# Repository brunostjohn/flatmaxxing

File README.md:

<div align="center">

# flatmaxx

**Turn a KiCad PCB into a complete CNC, laser, and electroplating job set - one command, end to end.**

</div>

`flatmaxx` takes a finished KiCad board and drives your entire home-fab bench for you: it generates Gerbers and drill files, plans isolation milling and non-copper-clearing G-code with FlatCAM, sorts every hole into the bit you actually own, burns solder-mask and solder-paste stencils on an xTool laser, drills plated/non-plated holes and cuts the board outline on a Makera CNC, and even works out the electroplating bath recipe — all from a single command, behind a live terminal UI.

> [!NOTE]
> This tool is built around one specific bench: a **Makera Carvera (Air)** CNC, **xTool M1 Ultra / F1 Ultra** lasers, and a **DIY copper electroplating** setup. It's shared as-is. Nothing stops you using it, but you'll want to retune the config to your own hardware, tools, and chemistry before trusting the output to a machine.

## Contents

- [No support — use entirely at your own risk](#-no-support--use-entirely-at-your-own-risk)
- [Installation](#installation)
- [Features](#features)
- [How it works](#how-it-works)
- [Prerequisites](#prerequisites)
- [Usage](#usage)
- [Configuration](#configuration)
- [Output layout](#output-layout)
- [Terminal experience](#terminal-experience)
- [Development](#development)

## ⚠️ No support — use entirely at your own risk

> [!CAUTION]
> **This project is provided strictly AS IS, with NO SUPPORT of any kind.**
>
> - **No tech support.** Issues opened to ask for help, setup assistance, or troubleshooting **will not be answered** and may be closed without comment.
> - **No bug guarantees.** Even legitimate bug reports **may never get a response or a fix.** Don't assume one is coming.
> - **No warranty.** Nothing here is promised to work, to keep working, or to be safe for your hardware, your materials, or you. You run it at your own risk.
>
> This is a **hobby project** I share for free in my spare time. I have a full-time job and a life, and I'm not interested in spending my free time doing unpaid tech support — I don't want my hobby to become my job. If that's a problem for you, **don't use this.**
>
> Pull requests with fixes are welcome, but I make **no commitment** to review, respond to, or merge them.

## Installation

`flatmaxx` ships as a single, codesigned **macOS arm64 (Apple Silicon)** binary. Pick whichever install path you prefer.

### Homebrew

```sh
brew tap brunostjohn/flatmaxxing https://github.com/brunostjohn/flatmaxxing
brew trust flatmaxx
brew install flatmaxx
```

Upgrade later with `brew upgrade flatmaxx`.

### Install script

Downloads the latest release into `~/.local/bin`, checksum-verified, using only standard macOS tools:

```sh
curl -fsSL https://raw.githubusercontent.com/brunostjohn/flatmaxxing/main/scripts/install.sh | sh
```

If `~/.local/bin` isn't on your `PATH`, the script prints the exact line to add. Pin a version with `FLATMAXX_VERSION=1.2.3`, or change the target with `FLATMAXX_INSTALL_DIR=...`. Installed this way, `flatmaxx update` upgrades in place (see [Updating](#updating)).

### From source

`flatmaxx` builds with [Bun](https://bun.sh) — the only thing you need.

```sh
git clone https://github.com/brunostjohn/flatmaxxing flatmaxx
cd flatmaxx
bun install
bun run build:native   # compile the native macOS accessibility module
```

Run it straight from source:

```sh
bun src/index.ts <kicad-project>
```

Or build the standalone, codesigned binary at `dist/flatmaxx`:

```sh
bun run build
./dist/flatmaxx <kicad-project>
```

### Updating

If you installed via the script (or any binary in a writable location), upgrade in place:

```sh
flatmaxx update           # check for and install the latest release, with a progress bar
flatmaxx update --check   # only report whether a newer release exists
```

Homebrew installs are managed by brew — run `brew upgrade flatmaxx` instead.

## Features

- **One command, full pipeline** — `flatmaxx <project>` runs every stage from board validation to machine-ready files.
- **Isolation + non-copper clearing** — FlatCAM-driven V-bit isolation routing and pocket clearing, exported as Carvera G-code per side.
- **Drill categorization** — parses Excellon output and snaps every hole to the nearest bit in *your* declared drill set, warning on holes too small to machine.
- **Solder mask & paste stencil** — automates xTool Studio over the Chrome DevTools Protocol to import geometry and set laser power/speed/passes per device.
- **Drilling & edge cut** — automates MakeraCAM via macOS Accessibility to drill plated/non-plated holes and cut the board outline with retaining tabs.
- **Electroplating report** — computes bath dimensions, current density, timing, and chemistry from your board bounds and recipe.
- **Design rule checks** — isolation feasibility (DRC) and drill machinability gates that can warn or hard-fail before any machine moves.
- **Inline board preview** — renders the board image right in your terminal (kitty / iTerm2 / sixel).
- **Composable TOML config** — project + user config with `extends` inheritance, deep merge, and per-run CLI overrides.

## How it works

`flatmaxx` runs an ordered pipeline. Each stage feeds the next; you can disable the ones you don't need from config.

| # | Stage | Consumes | Produces | Driven via |
|---|-------|----------|----------|------------|
| 1 | Preflight | config | software & permission check | `doctor` checks |
| 2 | Validate board | `.kicad_pcb` | manufacturability report | `kicadts` |
| 3 | KiCad outputs | `.kicad_pcb` | Gerbers, drills, SVG, PNG + inline preview | `kicad-cli` |
| 4 | Categorize drills | Excellon | per-bit drill files | Excellon parser |
| 5 | Isolation DRC | Gerbers | clearance violations | FlatCAM (headless) |
| 6 | CNC jobs | Gerbers | isolation + NCC G-code (Carvera) | FlatCAM (headless) |
| 7 | Alignment drills | `.kicad_pcb` | registration holes | Excellon |
| 8 | Edge-cut DXFs | `.kicad_pcb` | `*-PTH_EdgeCuts.dxf`, `*-Final_EdgeCuts.dxf` | DXF generator |
| 9 | Electroplating report | board bounds + recipe | bath dimensions & timing | — |
| 10 | xTool projects | mask SVG + stencil DXF | solder mask + paste stencil jobs | xTool Studio (CDP) |
| 11 | Plated holes | PTH DXF + drills | drilling + plating outline G-code | MakeraCAM (AX) |
| 12 | Final cut | Final DXF + drills | non-plated drilling + edge contour | MakeraCAM (AX) |

## Prerequisites

> [!IMPORTANT]
> **macOS only.** The laser and CNC stages rely on native macOS Accessibility automation and AppleScript, so `flatmaxx` does not run on Linux or Windows.

External software (only the stages you enable need their tools):

| Tool | Needed for | Default location |
|------|-----------|------------------|
| [KiCad](https://www.kicad.org) (with `kicad-cli`) | always — board parsing & exports | `/Applications/KiCad/KiCad.app/Contents/MacOS/kicad-cli` |
| [FlatCAM](https://bitbucket.org/jpcgt/flatcam) | isolation DRC + CNC G-code | `flatcam` (on `PATH`) |
| [xTool Studio](https://www.xtool.com/pages/software) | solder mask + paste stencil | `/Applications/xTool Studio.app` |
| [MakeraCAM](https://www.makera.com) | drilling + edge cut | `/Applications/MakeraCAM.app` |

The xTool and MakeraCAM stages also require **macOS Accessibility permission** (System Settings → Privacy & Security → Accessibility) and a Chrome DevTools port open for xTool Studio (`127.0.0.1:9333` by default).

> [!TIP]
> Run `flatmaxx doctor <project>` before your first real build — it checks every required executable, app, and permission for your enabled stages and tells you exactly what's missing, without touching a machine.

## Usage

Initialize a config in your KiCad project, then build:

```sh
flatmaxx init                 # create flatmaxxing.toml for the current project
flatmaxx ~/projects/myboard   # run the full pipeline
```

### Commands

| Command | What it does |
|---------|--------------|
| `flatmaxx <project>` | Creates CNC files from a KiCad project (same as `build`). |
| `flatmaxx build <project>` | Explicit form of the root command. |
| `flatmaxx init` | Creates a `flatmaxxing.toml` config for the current project. |
| `flatmaxx config` | Opens an interactive editor for project config overrides. |
| `flatmaxx config --user` | Edits the shared `~/flatmaxxing.user.toml`. |
| `flatmaxx skills install [--global]` | Installs the flatmaxxing agent skill into the project (or for the current user with `--global`). |
| `flatmaxx doctor <project>` | Checks required software and permissions; generates nothing. |
| `flatmaxx validate <project> --fix` | Runs validation only — no FlatCAM, xTool, or MakeraCAM launches. |
| `flatmaxx clean <project> [--dry-run]` | Removes (or lists) generated output folders. |
| `flatmaxx update [--check]` | Updates flatmaxx in place to the latest GitHub release (script / binary installs; use `brew upgrade` for Homebrew). |

### Examples

```sh
# Use an explicit config file
flatmaxx build . --config flatmaxxing.toml

# Override any config value for a single run
flatmaxx build . --set cnc.isolation.feedRate=150

# Point at a custom kicad-cli executable
flatmaxx ~/projects/myboard -k /opt/kicad/kicad-cli

# Check the board and config without launching any apps
flatmaxx validate . --fix

# See what clean would delete, without deleting it
flatmaxx clean . --dry-run
```

## Configuration

`flatmaxx` reads a `flatmaxxing.toml` in the project, layered over a shared `~/flatmaxxing.user.toml`. Configs can pull in others via `extends`, are deep-merged (later wins), and any value can be overridden per run with `--set path=value` / `--unset path`.

Rather than hand-writing the whole file, run `flatmaxx init` to scaffold one, then `flatmaxx config` for an interactive editor. Every option, with its default value and allowed values, is documented in [`flatmaxxing.example.toml`](flatmaxxing.example.toml). A representative slice — your real tooling and isolation parameters:

```toml
extends = ["~/flatmaxxing.user.toml"]

[board]
file = "myboard.kicad_pcb"   # auto-detected if omitted

[cnc]
availableDrills = [
  { diameter = 0.4 }, { diameter = 0.5 }, { diameter = 0.7 },
  { diameter = 0.8 }, { diameter = 1.0 }, { diameter = 1.2 },
]
availableMills = [
  { diameter = 0.7 }, { diameter = 1.0 }, { diameter = 1.5 },
]

[cnc.isolation]
feedRate = 120
spindleSpeed = 15000
zCutDepth = 0.05
tool = { type = "vbit", diameter = 0.14, angle = 60 }
passes = 3
overlap = 60
```

<details>
<summary>Top-level config sections</summary>

`dependencies` (tool paths) · `paths` (output folders) · `board` · `alignmentDrills` · `electroplating` (container + recipe) · `solderMask` · `stencil` · `drills` · `place` · `cnc` (`isolation`, `nonCopperClearing`, `clearance`, `backside`, `drilling`, `availableDrills`, `availableMills`) · `xtool` · `makeracam` · `validation` (ranges + feasibility gates).

</details>

## Output layout

A full run writes machine-ready files into your project (folders are configurable under `[paths]`):

```
myboard/
├── gerbers/    # KiCad Gerber + edge-cut DXF exports
├── drills/     # categorized Excellon drill files (one per bit)
├── gcodes/     # isolation + non-copper-clearing G-code (Carvera)
├── dxf/        # board outline DXFs
├── png/        # rendered board & mask images
├── svg/        # vector solder-mask art
├── xtool/      # xTool Studio projects (solder mask + stencil)
└── cnc/        # MakeraCAM projects + exported drilling/contour G-code
```

The electroplating bath report (dimensions, current density, timing, chemistry) is generated alongside.

## Terminal experience

`flatmaxx` runs on an [Ink](https://github.com/vadimdemedes/ink) UI: a live, hierarchical task list shows every stage and substep with spinners, progress bars, and inline error detail. When your terminal supports it (kitty, iTerm2, or sixel), the rendered board image is drawn directly in the scrollback so you can eyeball the layout before any machine moves.

## Development

```sh
bun run dev         # build native + run against the bundled testdir/ project
bun test            # run the test suite
bun run typecheck   # type-check with tsgo
bun run format      # format with Biome
```

The codebase is built on Effect v4 and follows the conventions in [`CLAUDE.md`](CLAUDE.md); the native macOS accessibility bindings live in the Rust workspace under [`native/`](native).

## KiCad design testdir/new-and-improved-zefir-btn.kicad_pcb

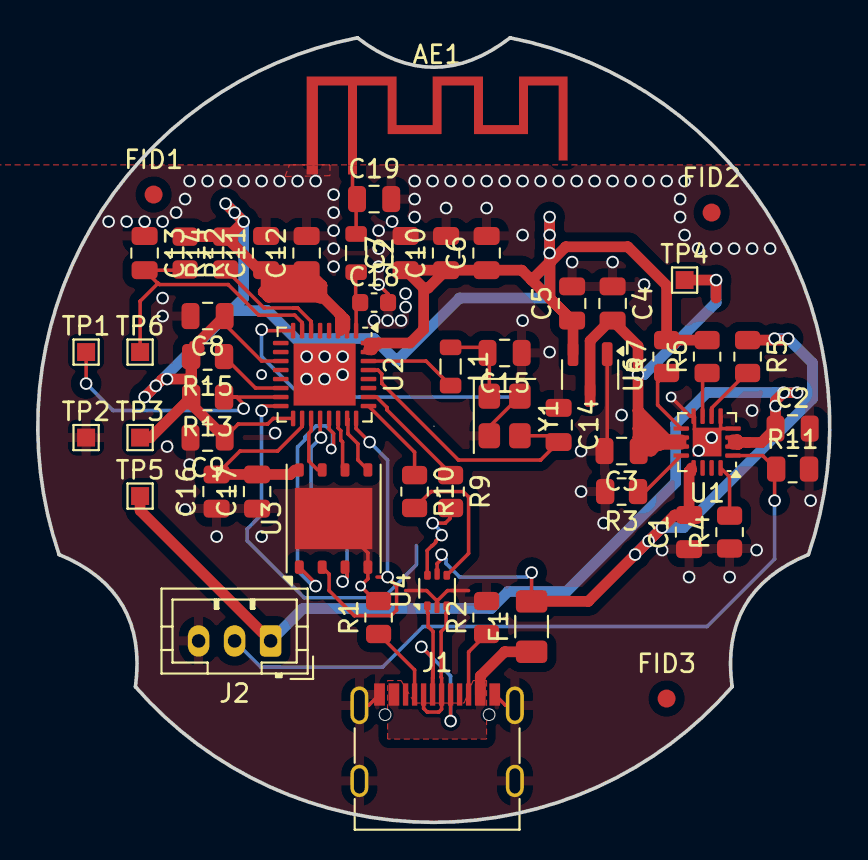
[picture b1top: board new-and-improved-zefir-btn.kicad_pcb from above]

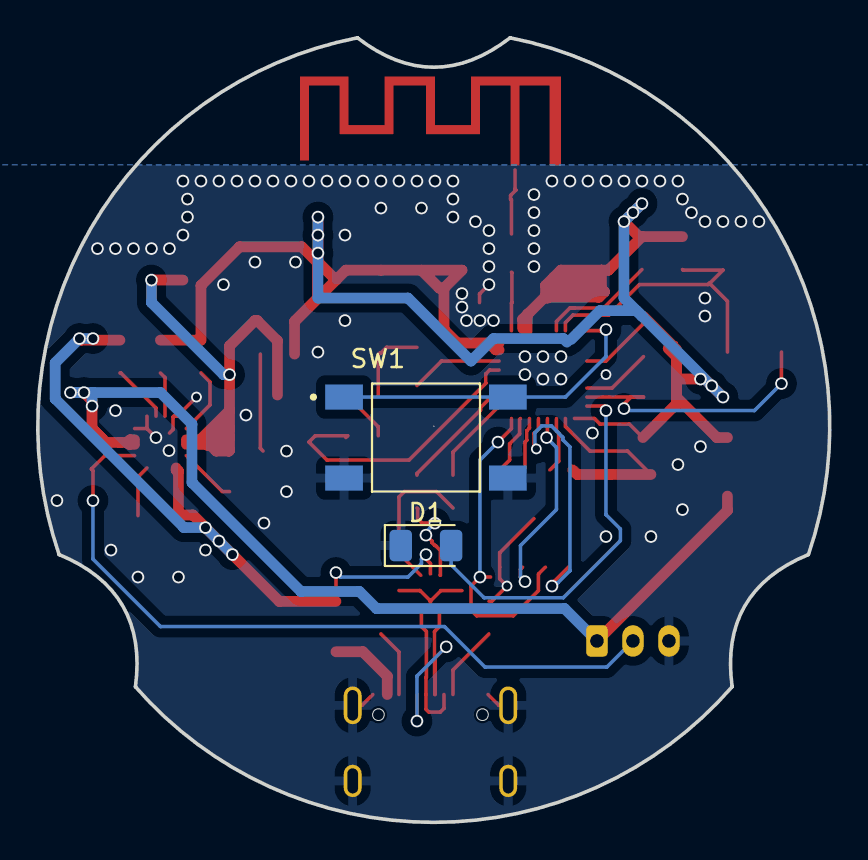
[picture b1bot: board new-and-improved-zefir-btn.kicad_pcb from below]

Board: 2 copper layers, 44.0 x 43.6 mm, 56 parts (2 on the bottom side), 38 nets.

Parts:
AE1: Antenna_Shield; ESPRESSIF_ESP32_MIFA_2.4GHz_Right
C1, C12, C13, C16, C17: 1uF; C_0805_2012Metric
C2, C3: 4.7uF; C_0805_2012Metric
C4, C5, C6, C7: 10uF; C_0805_2012Metric
C8, C9, C10, C11: 100nF; C_0805_2012Metric
C14, C15: C_Small; C_0805_2012Metric
C18: 5.3pF; C_0603_1608Metric
C19: 3.9pF; C_0805_2012Metric
D1: LED; LED_1206_3216Metric
F1: 500mA; Fuse_1206_3216Metric
FID1, FID2, FID3: Fiducial; Fiducial_1mm_Mask2mm
J1: USB_C_Receptacle_USB2.0_16P; USB_C_Receptacle_G-Switch_GT-USB-7010ASV
J2: Conn_01x03_Socket; JST_PH_B3B-PH-K_1x03_P2.00mm_Vertical
L1: 24nH; L_0805_2012Metric
L2: 1.8nH; L_0805_2012Metric
R1, R2: 5.1k; R_0805_2012Metric
R3: 3.1k; R_0805_2012Metric
R4: 5.9k; R_0805_2012Metric
R5, R6, R7: 100k; R_0805_2012Metric
R9, R10: 22R; R_0805_2012Metric
R11, R12, R13, R14, R15: 10k; R_0805_2012Metric
SW1: SW_Push_Dual; SW_TS04-66-95-BK-100-SMT
TP1: Boot; TestPoint_Pad_1.0x1.0mm
TP2: GND; TestPoint_Pad_1.0x1.0mm
TP3: 3v3; TestPoint_Pad_1.0x1.0mm
TP4: VSys; TestPoint_Pad_1.0x1.0mm
TP5: VBatt; TestPoint_Pad_1.0x1.0mm
TP6: Reset; TestPoint_Pad_1.0x1.0mm
U1: BQ24074RGT; VQFN-16-1EP_3x3mm_P0.5mm_EP1.6x1.6mm
U2: ESP32-C3; QFN-32-1EP_5x5mm_P0.5mm_EP3.45x3.45mm
U3: W25Q32JVZP; WSON-8-1EP_6x5mm_P1.27mm_EP3.4x4.3mm
U4: USBLC6-2P6; SOT-666
U6: XC6206PxxxMR; SOT-23-3
Y1: 40MHz; Crystal_SMD_3225-4Pin_3.2x2.5mm

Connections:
+3V3: C5.1, C6.1, C7.1, C8.1, C9.1, C10.1, C11.1, C12.1, R6.2, R7.2, R12.1, R13.2, R14.2, R15.2, TP3.1, U2.2 (VDD3P3), U2.3 (VDD3P3), U2.11 (VDD3P3_RTC), U2.17 (VDD3P3_CPU), U2.31 (VDDA), U2.32 (VDDA), U6.2 (VO)
/BattTemp: J2.2, R11.1, U1.1 (TS)
/CHG: R7.1, U1.9 (~CHG)
/D_N: R10.2, U4.4 (I/O2)
/D_P: R9.2, U4.6 (I/O1)
/D_USB_N: J1.A7 (D-), J1.B7 (D-), U4.3 (I/O2)
/D_USB_P: J1.A6 (D+), J1.B6 (D+), U4.1 (I/O1)
/FLASH_CLK: U2.22 (SPICLK/GPIO15), U3.6 (CLK)
/FLASH_CS: U2.21 (SPICS0/GPIO14), U3.1 (~CS)
/FLASH_IO0: U2.23 (SPID/GPIO16), U3.5 (DI/IO_{0})
/FLASH_IO1: U2.24 (SPIQ/GPIO17), U3.2 (DO/IO_{1})
/FLASH_IO2: U2.20 (SPIWP/GPIO13), U3.3 (~WP/IO_{2})
/FLASH_IO3: U2.19 (SPIHD/GPIO12), U3.7 (~HOLD/~RESET/IO_{3})
/PGOOD: R6.1, U1.7 (~PGOOD)
/SYS_LED: D1.2 (A), U2.16 (GPIO10)
/TALK_BTN: SW1.1, SW1.3, U2.8 (GPIO3/ADC1_CH3)
GND: AE1.2 (Shield), C1.1, C2.2, C3.2, C4.1, C5.2, C6.2, C7.2, C8.2, C9.2, C10.2, C11.2, C12.2, C13.1, C14.1, C15.1, C16.1, C17.1, C18.2, C19.2, D1.1 (K), J1.A1 (GND), J1.A12 (GND), J1.B1 (GND), J1.B12 (GND), J1.S1 (SHIELD), J2.3, R1.2, R2.2, R3.2, R4.1, R11.2, SW1.2, SW1.4, TP2.1, U1.4 (~CE), U1.5 (EN2), U1.8 (VSS), U1.17 (VSS), U2.33 (GND), U3.4 (GND), U3.9 (EP), U4.2 (GND), U6.1 (GND), Y1.2, Y1.4
unnamed: AE1.1 (A), C19.1, L2.1
unnamed: C15.2, L1.1, Y1.1
unnamed: F1.1, J1.A4 (VBUS), J1.A9 (VBUS), J1.B4 (VBUS), J1.B9 (VBUS)
unnamed: J1.A5 (CC1), R1.1
unnamed: J1.B5 (CC2), R2.1
unnamed: R5.2, U1.6 (EN1)
unnamed: R3.1, U1.12 (ILIM)
unnamed: R4.2, U1.16 (ISET)
unnamed: C13.2, R12.2, TP6.1, U2.7 (CHIP_EN)
unnamed: R14.1, U2.6 (GPIO2/ADC1_CH2)
unnamed: R15.1, U2.14 (GPIO8)
unnamed: R13.1, TP1.1, U2.15 (GPIO9/BOOT)
unnamed: R10.1, U2.25 (GPIO18/USB_D-)
unnamed: R9.1, U2.26 (GPIO19/USB_D+)
unnamed: C18.1, L2.2, U2.1 (LNA_IN)
unnamed: C14.2, U2.29 (XTAL_N), Y1.3
unnamed: L1.2, U2.30 (XTAL_P)
VBUS: C1.2, F1.2, R5.1, U1.13 (IN), U4.5 (VBUS)
VBatt: C2.1, J2.1, TP5.1, U1.2 (BAT), U1.3 (BAT)
VFlash: C16.2, C17.2, U2.18 (VDD_SPI/GPIO11), U3.8 (VCC)
VSys: C3.1, C4.2, TP4.1, U1.10 (OUT), U1.11 (OUT), U6.3 (VI)

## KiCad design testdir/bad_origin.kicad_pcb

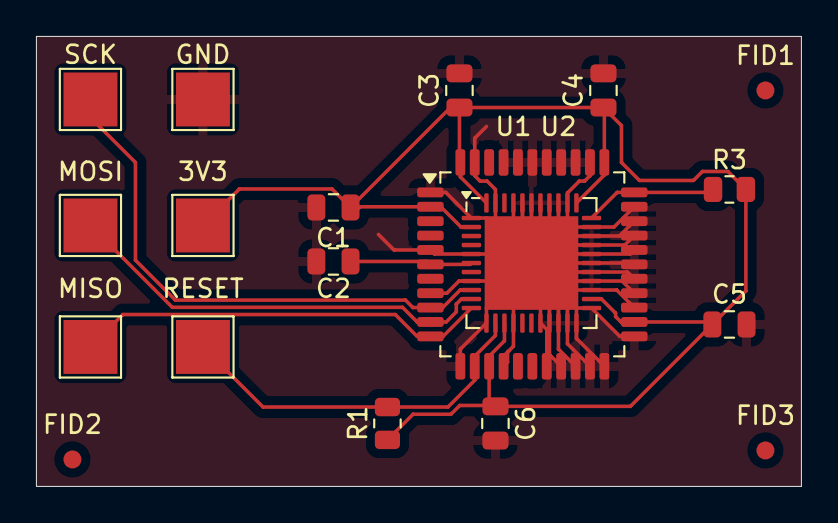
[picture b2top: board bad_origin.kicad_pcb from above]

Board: 2 copper layers, 42.5 x 25.0 mm, 19 parts (0 on the bottom side), 8 nets.

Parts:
C1, C2: 1uF; C_0805_2012Metric
C3, C4, C5, C6: 0.1uF; C_0805_2012Metric
FID1, FID2, FID3: Fiducial; Fiducial_1mm_Mask2mm
R1, R3: 10k; R_0805_2012Metric
TP1: RESET; TestPoint_Pad_3.0x3.0mm
TP2: 3V3; TestPoint_Pad_3.0x3.0mm
TP3: GND; TestPoint_Pad_3.0x3.0mm
TP4: MISO; TestPoint_Pad_3.0x3.0mm
TP5: MOSI; TestPoint_Pad_3.0x3.0mm
TP6: SCK; TestPoint_Pad_3.0x3.0mm
U1: ATmega32U4-A; TQFP-44_10x10mm_P0.8mm
U2: ATmega32U4-M; QFN-44-1EP_7x7mm_P0.5mm_EP5.2x5.2mm

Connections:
+3V3: C1.1, C3.1, C4.1, C5.1, C6.1, R1.1, R3.2, TP2.1, U1.2 (UVCC), U1.14 (VCC), U1.24 (AVCC), U1.34 (VCC), U1.44 (AVCC), U2.2 (UVCC), U2.14 (VCC), U2.24 (AVCC), U2.34 (VCC), U2.44 (AVCC)
/HWB: R3.1, U1.33 (~HWB/PE2), U2.33 (~HWB/PE2)
/MISO: TP4.1, U1.11 (PB3), U2.11 (PB3)
/MOSI: TP5.1, U1.10 (PB2), U2.10 (PB2)
/RESET: R1.2, TP1.1, U1.13 (~RESET), U2.13 (~RESET)
/SCK: TP6.1, U1.9 (PB1), U2.9 (PB1)
/UCAP: C2.2, U1.6 (UCAP), U2.6 (UCAP)
GND: C1.2, C2.1, C3.2, C4.2, C5.2, C6.2, TP3.1, U1.1 (PE6), U1.5 (UGND), U1.8 (PB0), U1.12 (PB7), U1.15 (GND), U1.18 (PD0), U1.19 (PD1), U1.20 (PD2), U1.21 (PD3), U1.22 (PD5), U1.23 (GND), U1.25 (PD4), U1.26 (PD6), U1.27 (PD7), U1.28 (PB4), U1.29 (PB5), U1.30 (PB6), U1.31 (PC6), U1.32 (PC7), U1.35 (GND), U1.36 (PF7), U1.37 (PF6), U1.38 (PF5), U1.39 (PF4), U1.40 (PF1), U1.41 (PF0), U1.43 (GND), U2.1 (PE6), U2.5 (UGND), U2.8 (PB0), U2.12 (PB7), U2.15 (GND), U2.18 (PD0), U2.19 (PD1), U2.20 (PD2), U2.21 (PD3), U2.22 (PD5), U2.23 (GND), U2.25 (PD4), U2.26 (PD6), U2.27 (PD7), U2.28 (PB4), U2.29 (PB5), U2.30 (PB6), U2.31 (PC6), U2.32 (PC7), U2.35 (GND), U2.36 (PF7), U2.37 (PF6), U2.38 (PF5), U2.39 (PF4), U2.40 (PF1), U2.41 (PF0), U2.43 (GND), U2.45 (GND)

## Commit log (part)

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2026-06-19 start
2026-06-20 generates kicad outputs
2026-06-20 xtool semi-working
2026-06-20 xtool solder mask stuff creates fine now (yay)
2026-06-20 refactord
2026-06-21 cleanup and shit
2026-06-21 new helpers
2026-06-21 almost done
2026-06-21 xtool projects now get created successfully
2026-06-21 almost
2026-06-21 xtool fully done LFG
2026-06-21 xtool workflow now does all the things
2026-06-21 configmaxxed chad
2026-06-21 no isolation yet, but close
2026-06-21 tunable rpm
2026-06-21 drills get separated now
2026-06-21 unfuck numbering
2026-06-21 format everything
2026-06-22 temp commit before i delete a bunch of shit and clean up a bunch of other shit
2026-06-22 remove claude noise
2026-06-22 format the shit out of this
2026-06-22 do more natively
2026-06-22 before review
2026-06-23 cleanups
2026-06-23 cleanup kicad
2026-06-23 plating
2026-06-23 checks and such
2026-06-23 init command
2026-06-23 config editor!
2026-06-23 config, images, type shit
2026-06-27 cleanin up
2026-06-27 more cleanup
2026-06-28 working now !!
2026-06-28 fix board image shi
2026-06-28 imagemaxxing
2026-06-28 settings n stuff
2026-06-28 patch sharp to unfuck it
2026-06-28 leave me alone
2026-06-28 docs, updates, installers
2026-06-28 some new things
2026-06-28 sharp gtfo
2026-06-28 fuck ass macos ver
2026-06-28 chore: bump homebrew formula to v1.0.0
2026-06-28 micro update
2026-06-28 smol update
